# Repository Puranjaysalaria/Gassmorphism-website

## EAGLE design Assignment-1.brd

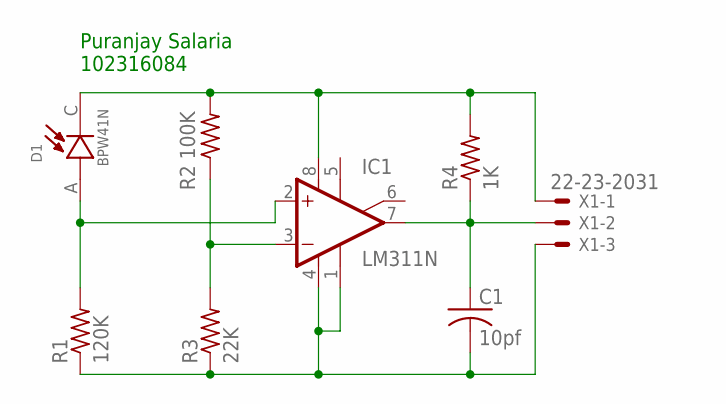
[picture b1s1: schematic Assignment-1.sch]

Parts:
C1: 10pf; C025-050X050
D1: BPW41N; DIO_BPW41N
IC1: LM311N; DIL08
R1: 120K; 0204/7
R2: R2 100K; 0204/7
R3: 22K; 0204/7
R4: 1K; 0204/7
X1: 22-23-2031

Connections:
unnamed: D1.A, IC1.2 (+IN), R1.2
unnamed: D1.C, IC1.8 (V+), R2.2, R4.2, X1.1
unnamed: IC1.3 (-IN), R2.1, R3.2
unnamed: C1.2, IC1.1 (GND), IC1.4 (V-), R1.1, R3.1, X1.3
unnamed: C1.1, IC1.7 (OUT), R4.1, X1.2

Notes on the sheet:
Puranjay Salaria 102316084

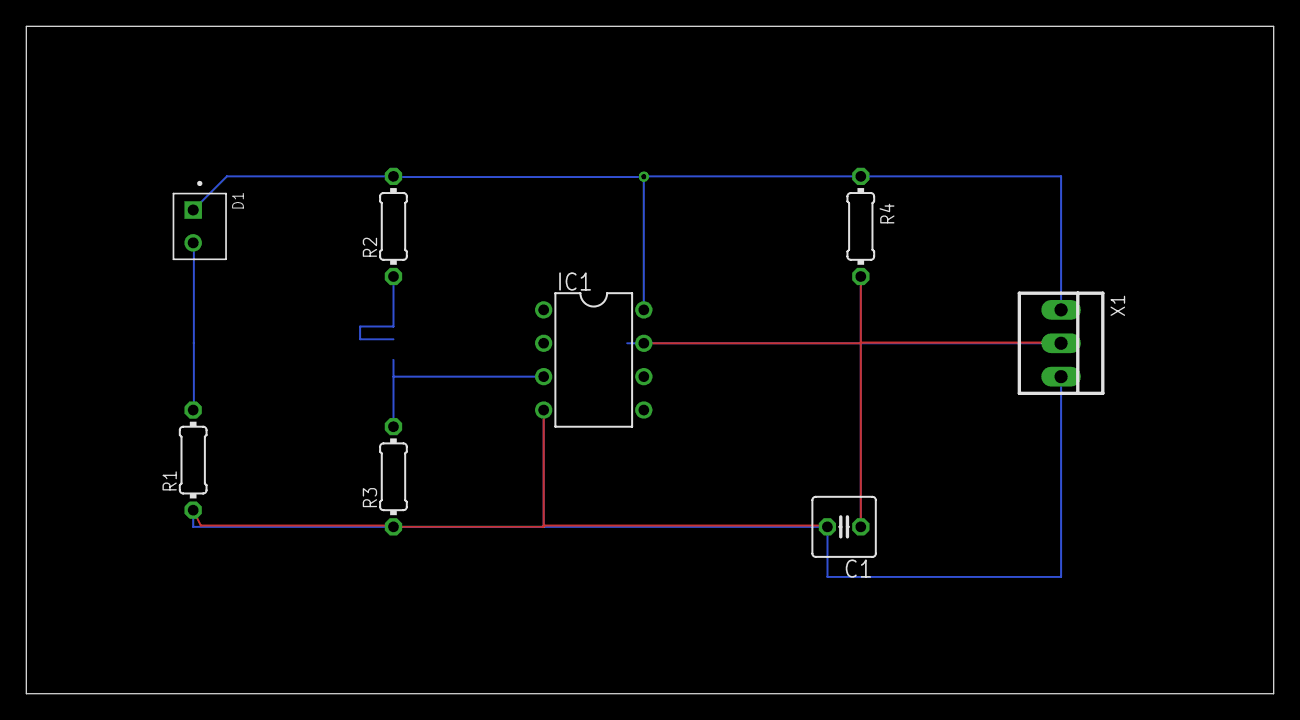
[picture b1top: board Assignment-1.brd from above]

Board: 2 copper layers, 94.9 x 50.8 mm, 8 parts (0 on the bottom side), 5 nets.

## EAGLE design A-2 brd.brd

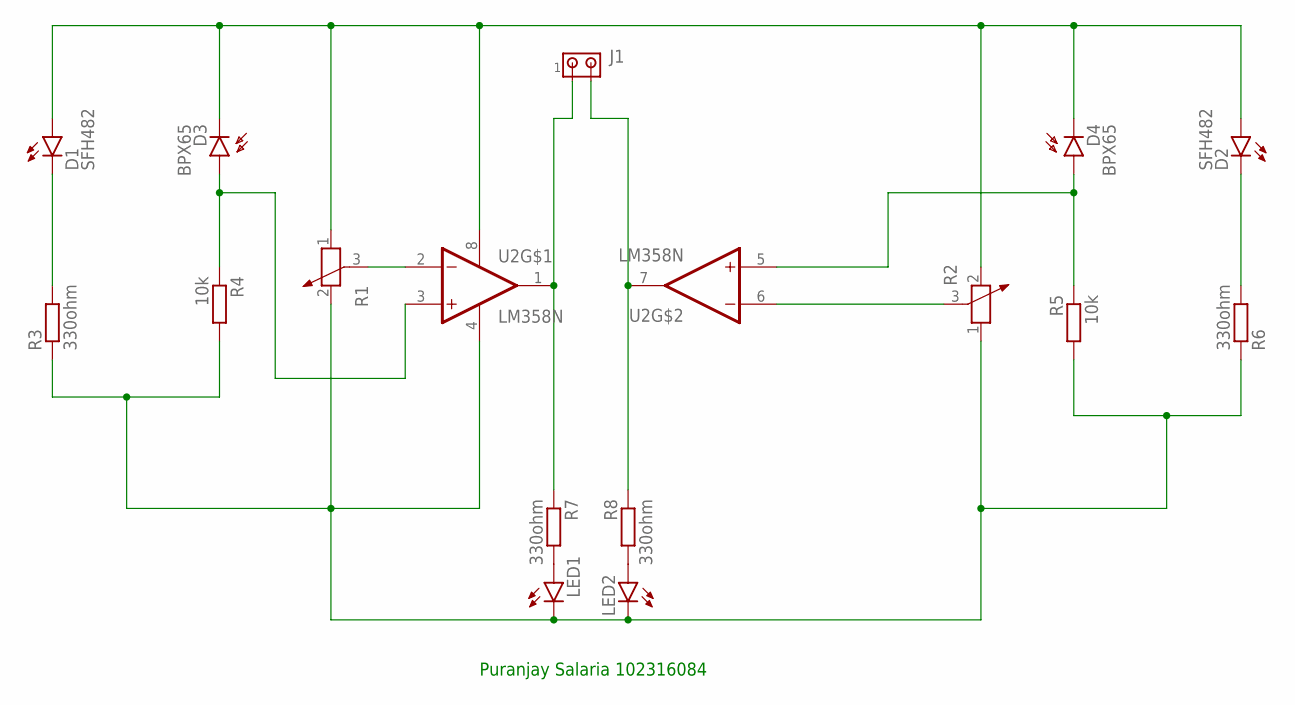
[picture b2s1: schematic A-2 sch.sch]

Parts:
D1, D2: SFH482
D3, D4: BPX65
J1: MTA02-100; 10X02MTA
LED1, LED2: LED3MM
R1, R2: POTENTIOMETER_PT-10; PT-10
R3, R6, R7, R8: 330ohm; 0204/5
R4, R5: 10k; 0204/5
U2: LM358N; DIP762W46P254L960H508Q8

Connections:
unnamed: LED1.A, R7.2
unnamed: D1.A, D2.A, D3.K (C), D4.K (C), R1.1, R2.2, U2.8 (VCC)
unnamed: D1.K (C), R3.2
unnamed: D3.A, R4.1, U2.3 (1IN+)
unnamed: LED1.K (C), LED2.K (C), R1.2, R2.1, R3.1, R4.2, R5.2, R6.1, U2.4 (GND)
unnamed: J1.1, R7.1, U2.1 (1OUT)
unnamed: R1.3, U2.2 (1IN-)
unnamed: LED2.A, R8.2
unnamed: J1.2, R8.1, U2.7 (2OUT)
unnamed: D2.K (C), R6.2
unnamed: D4.A, R5.1, U2.5 (2IN+)
unnamed: R2.3, U2.6 (2IN-)

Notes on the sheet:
Puranjay Salaria 102316084

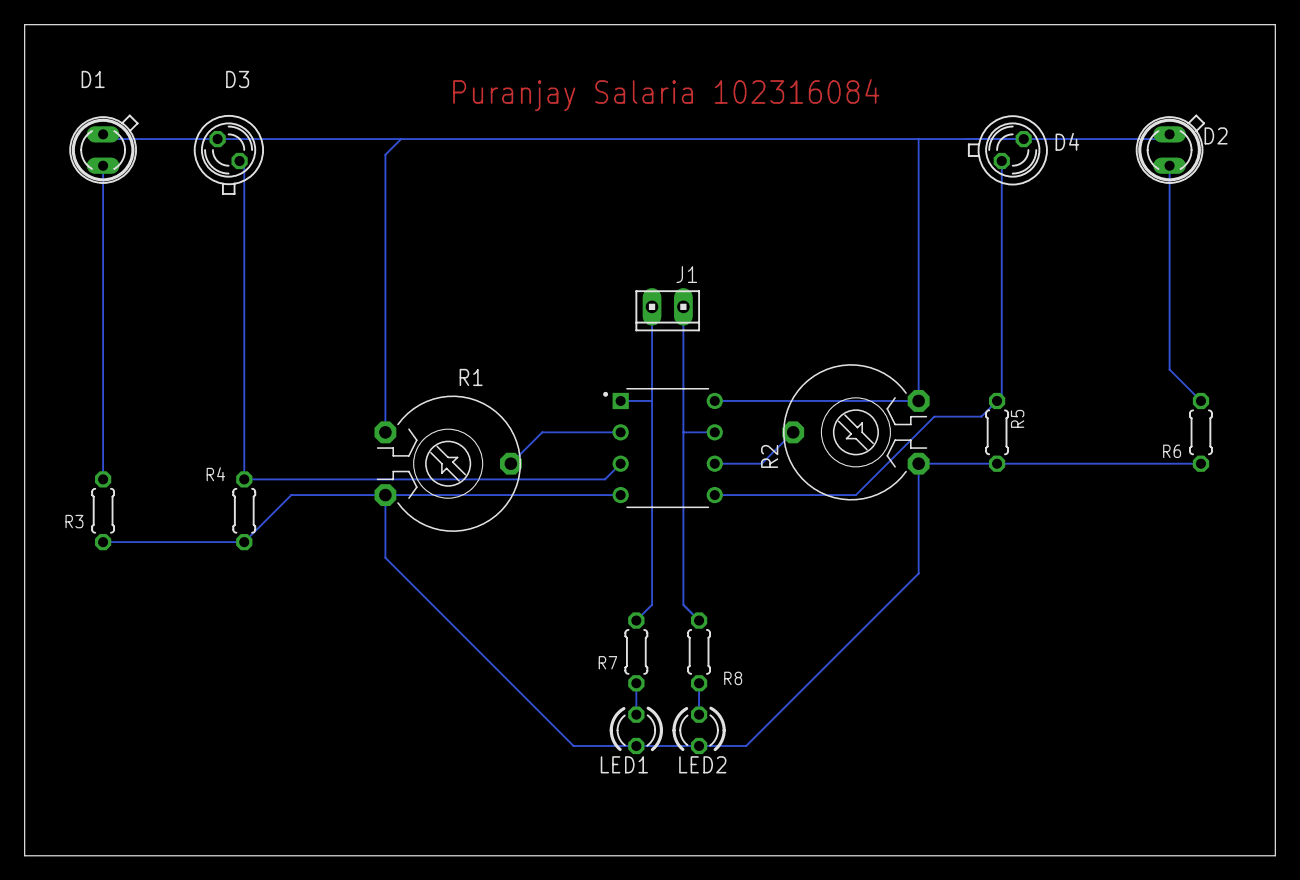
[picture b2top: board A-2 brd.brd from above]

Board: 2 copper layers, 101.3 x 67.3 mm, 16 parts (0 on the bottom side), 12 nets.

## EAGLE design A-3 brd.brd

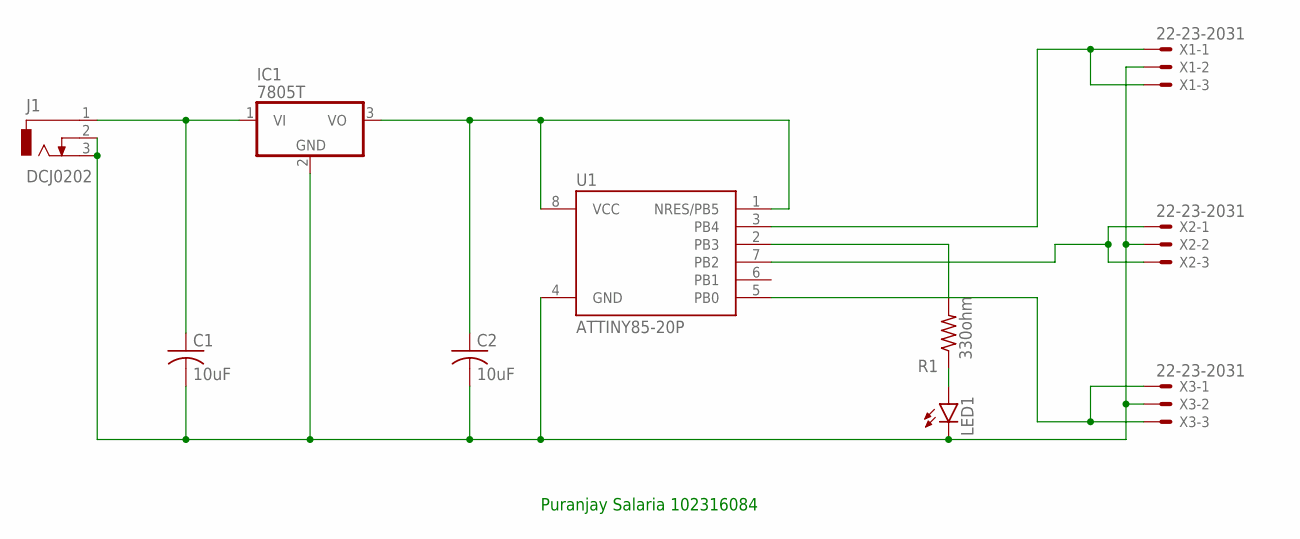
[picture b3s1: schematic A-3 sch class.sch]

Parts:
C1, C2: 10uF; C025-024X044
IC1: 7805T; TO220H
J1: DCJ0202
LED1: LED3MM
R1: 330ohm; 0207/5V
U1: ATTINY85-20P; PDIP08_300MIL
X1, X2, X3: 22-23-2031

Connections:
unnamed: C1.1, IC1.1 (VI), J1.1
unnamed: LED1.A, R1.1
unnamed: C1.2, C2.2, IC1.2 (GND), J1.2, J1.3, LED1.K (C), U1.4 (GND), X1.2, X2.2, X3.2
unnamed: C2.1, IC1.3 (VO), U1.1 (NRES/PB5), U1.8 (VCC)
unnamed: R1.2, U1.2 (PB3)
unnamed: U1.3 (PB4), X1.1, X1.3
unnamed: U1.5 (PB0), X3.1, X3.3
unnamed: U1.7 (PB2), X2.1, X2.3

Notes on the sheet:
Puranjay Salaria 102316084

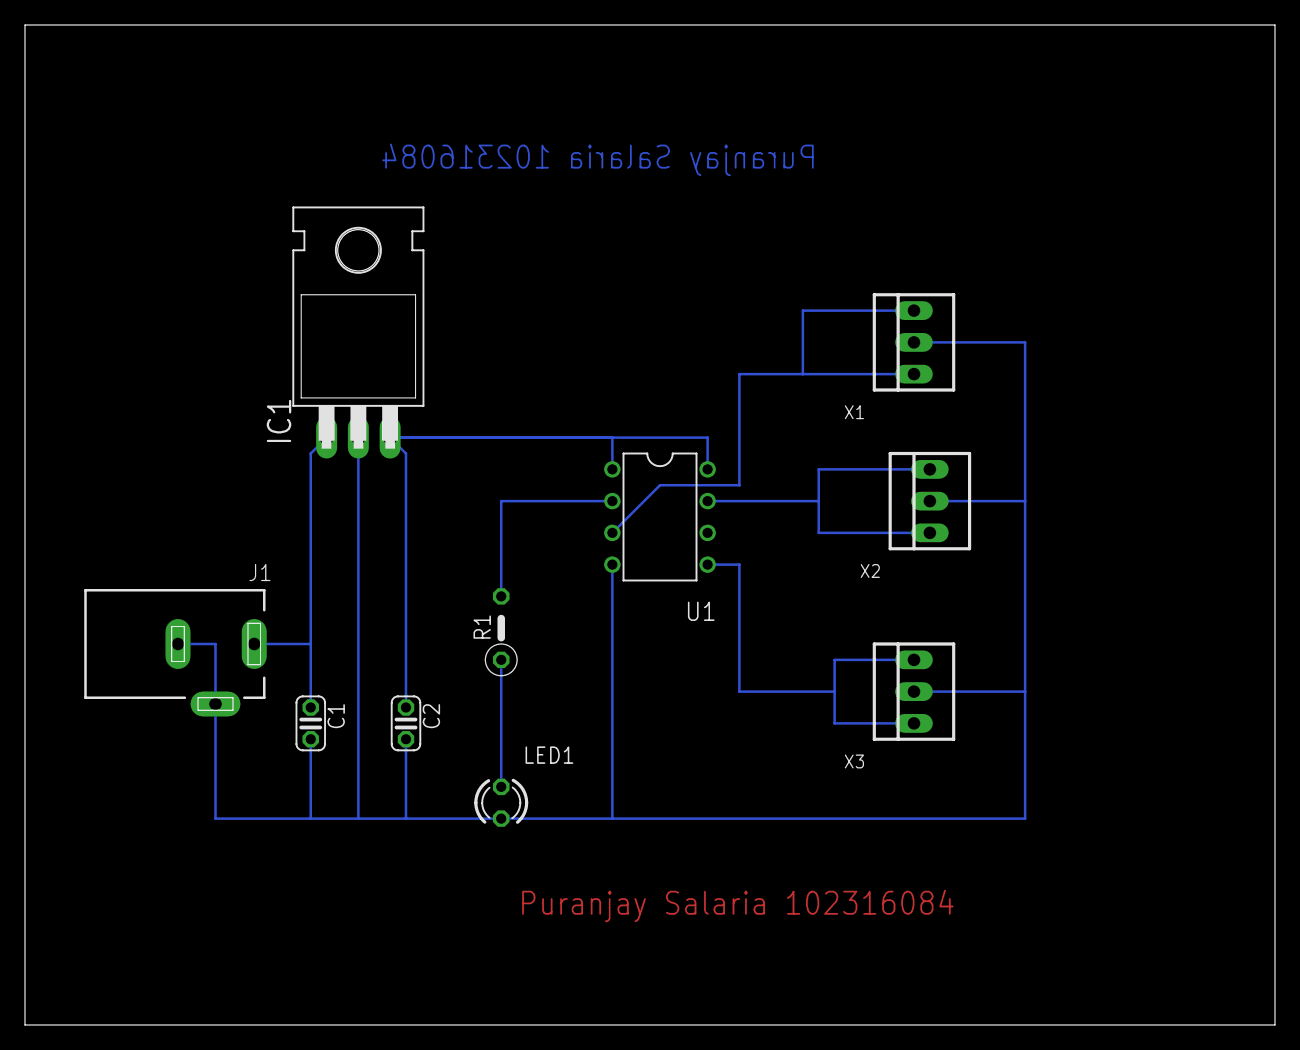
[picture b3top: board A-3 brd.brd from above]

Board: 2 copper layers, 100.0 x 80.0 mm, 10 parts (0 on the bottom side), 8 nets.

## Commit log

2023-11-18 Gassmorphism
